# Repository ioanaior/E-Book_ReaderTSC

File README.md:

# E-Book_ReaderTSC

## 📘 Schema bloc

```mermaid
flowchart TB
  USB-C -->|5V| Charger["Battery Charger (MCP73832)"]
  Charger -->|Charging| LiPo["LiPo Battery"]
  LiPo --> LDO["3V3 LDO"]
  LiPo --> DC5["5V DC/DC"]

  ESP32["ESP32-C3-WROOM"]

  LDO -->|3.3V| ESP32
  LDO -->|3.3V| Display
  LDO -->|3.3V| SDCard
  LDO -->|3.3V| TempSensor
  LDO -->|3.3V| Buttons

  ESP32 -- SPI --> Display["1.5'' E-Ink Display (200x200px)"]
  ESP32 -- SPI --> SDCard["SD Card"]
  ESP32 -- GPIO --> Buttons["Buttons (3x)"]
  ESP32 -- I2C --> TempSensor["Temp/RH Sensor (BME680)"]
  ESP32 -- USB --> USB-C
```

# List of Components

Aici sunt listate componentele, impreuna cu linkurile pentru a verifica preturile si fisele tehnice. Unele componente nu au un model specificat, si în acele cazuri, fisele tehnice si linkurile catre preturi sunt marcate ca `#N/A`.
+ also SJ-ul si TP-urile sunt modelate de mine, deci nu am importat model 3D.

| Name of component  | Device                                    | Check Prices                                                                 | DataSheet                                                                  |
|--------------------|-------------------------------------------|-----------------------------------------------------------------------------|----------------------------------------------------------------------------|
| BOOT_BUTTON        | BUTTON_CUSYOMV1                           | [Check Price](https://industry.panasonic.com/global/en/products/control/switch/light-touch/number/evqpuj02k)  | [DataSheet](https://industry.panasonic.com/global/en/products/control/switch/light-touch/number/evqpuj02k) |
| C1                 | ESP32_WROVER_EAGLE-LTSPICE_CC0402         | [Check Price](https://industry.panasonic.com/global/en/products/control/switch/light-touch/number/evqpuj02k)  | [DataSheet](https://industry.panasonic.com/global/en/products/control/switch/light-touch/number/evqpuj02k) |
| C1_BAT             | ESP32_WROVER_EAGLE-LTSPICE_CC0402         | #N/A                                                                         | #N/A                                                                      |
| C1_BAT1            | EAGLE-LTSPICE_CC0402                      | #N/A                                                                         | #N/A                                                                      |
| C1_BAT2            | EAGLE-LTSPICE_CC0402                      | #N/A                                                                         | #N/A                                                                      |
| C2                 | ESP32_WROVER_EAGLE-LTSPICE_CC0402         | #N/A                                                                         | #N/A                                                                      |
| C2_BAT            | ESP32_WROVER_EAGLE-LTSPICE_CC0402         | #N/A                                                                         | #N/A                                                                      |
| C3                 | RCL_CPOL-EUCT3528                         | #N/A                                                                         | #N/A                                                                      |
| C4                 | ESP32_WROVER_EAGLE-LTSPICE_CC0402         | #N/A                                                                         | #N/A                                                                      |
| C4_USB             | ESP32_WROVER_EAGLE-LTSPICE_CC0402         | #N/A                                                                         | #N/A                                                                      |
| C5                 | ESP32_WROVER_EAGLE-LTSPICE_CC0402         | #N/A                                                                         | #N/A                                                                      |
| C5_USB             | ESP32_WROVER_EAGLE-LTSPICE_CC0402         | #N/A                                                                         | #N/A                                                                      |
| C6                 | ESP32_WROVER_EAGLE-LTSPICE_CC0402         | #N/A                                                                         | #N/A                                                                      |
| C7                 | ESP32_WROVER_EAGLE-LTSPICE_CC0402         | #N/A                                                                         | #N/A                                                                      |
| C8                 | ESP32_WROVER_EAGLE-LTSPICE_CC0402         | #N/A                                                                         | #N/A                                                                      |
| C9                 | EAGLE-LTSPICE_CC0402                      | #N/A                                                                         | #N/A                                                                      |
| C10                | ESP32_WROVER_EAGLE-LTSPICE_CC0402         | #N/A                                                                         | #N/A                                                                      |
| C10_SUPERCAP       | CPH3225A                                  | [Check Price](https://www.snapeda.com/parts/CPH3225A/Seiko+Instruments/view-part/?ref=eda) | [DataSheet](https://www.snapeda.com/parts/CPH3225A/Seiko+Instruments/view-part/?ref=eda) |
| CHANGE_BUTTON      | BUTTON_CUSYOMV1                           | [Check Price](https://industry.panasonic.com/global/en/products/control/switch-light-touch/number/evqpuj02k)  | [DataSheet](https://industry.panasonic.com/global/en/products/control/switch-light-touch/number/evqpuj02k) |
| CHG_LED            | ADAFRUIT_LEDCHIP-LED0603                  | [Check Price](https://www.snapeda.com/parts/KP-1608SURCK/Kingbright/view-part/?ref=search&t=LED%200603) | [DataSheet](https://www.snapeda.com/parts/KP-1608SURCK/Kingbright/view-part/?ref=search&t=LED%200603) |
| C_DELAY            | ESP32_WROVER_EAGLE-LTSPICE_CC0402         | #N/A                                                                         | #N/A                                                                      |
| D1                 | USBLC6-2SC6Y                              | [Check Price](https://www.snapeda.com/parts/USBLC6-2SC6Y/STMicroelectronics/view-part/?ref=eda) | [DataSheet](https://www.snapeda.com/parts/USBLC6-2SC6Y/STMicroelectronics/view-part/?ref=eda) |
| D2                 | ESP32_WROVER_AVX---SD0805S020S1R0_AVX_... | [Check Price](https://eu.mouser.com/ProductDetail/KYOCERA-AVX/SD0805S020S1R0?qs=jCA%252BPfw4LHbpkAoSnwrdjw%3D%3D) | [DataSheet](http://datasheets.avx.com/schottky.pdf)                       |
| D3                 | MBR0530                                   | [Check Price](https://eu.mouser.com/ProductDetail/KYOCERA-AVX/SD0805S020S1R0?qs=jCA%252BPfw4LHbpkAoSnwrdjw%3D%3D) | [DataSheet](https://eu.mouser.com/ProductDetail/KYOCERA-AVX/SD0805S020S1R0?qs=jCA%252BPfw4LHbpkAoSnwrdjw%3D%3D) |
| D4                 | MBR0530                                   | [Check Price](https://www.snapeda.com/parts/MBR0530/Onsemi/view-part/?ref=eda) | [DataSheet](https://www.snapeda.com/parts/MBR0530/Onsemi/view-part/?ref=eda) |
| D5                 | MBR0530                                   | [Check Price](https://www.snapeda.com/parts/MBR0530/Onsemi/view-part/?ref=eda) | [DataSheet](https://www.snapeda.com/parts/MBR0530/Onsemi/view-part/?ref=eda) |
| D6                 | PGB1010603MR                              | [Check Price](https://www.snapeda.com/parts/PGB1010603MR/Littelfuse/view-part/?ref=eda) | [DataSheet](https://www.snapeda.com/parts/PGB1010603MR/Littelfuse/view-part/?ref=eda) |
| D7                 | ESP32_WROVER_AVX---SD0805S020S1R0_AVX_... | [Check Price](https://eu.mouser.com/ProductDetail/KYOCERA-AVX/SD0805S020S1R0?qs=jCA%252BPfw4LHbpkAoSnwrdjw%3D%3D) | [DataSheet](http://datasheets.avx.com/schottky.pdf)                       |
| D8                 | PGB1010603MR                              | [Check Price](https://www.snapeda.com/parts/PGB1010603MR/Littelfuse/view-part/?ref=eda) | [DataSheet](https://www.snapeda.com/parts/PGB1010603MR/Littelfuse/view-part/?ref=eda) |
| D9                 | PGB1010603MR                              | [Check Price](https://www.snapeda.com/parts/PGB1010603MR/Littelfuse/view-part/?ref=eda) | [DataSheet](https://www.snapeda.com/parts/PGB1010603MR/Littelfuse/view-part/?ref=eda) |
| D10                | PGB1010603MR                              | [Check Price](https://www.snapeda.com/parts/PGB1010603MR/Littelfuse/view-part/?ref=eda) | [DataSheet](https://www.snapeda.com/parts/PGB1010603MR/Littelfuse/view-part/?ref=eda) |
| D11                | PGB1010603MR                              | [Check Price](https://www.snapeda.com/parts/PGB1010603MR/Littelfuse/view-part/?ref=eda) | [DataSheet](https://www.snapeda.com/parts/PGB1010603MR/Littelfuse/view-part/?ref=eda) |
| D12                | PGB1010603MR                              | [Check Price](https://www.snapeda.com/parts/PGB1010603MR/Littelfuse/view-part/?ref=eda) | [DataSheet](https://www.snapeda.com/parts/PGB1010603MR/Littelfuse/view-part/?ref=eda) |
| EPD_C1             | ESP32_WROVER_EAGLE-LTSPICE_CC0402         | #N/A                                                                         | #N/A                                                                      |
| EPD_C2             | ESP32_WROVER_EAGLE-LTSPICE_CC0402         | #N/A                                                                         | #N/A                                                                      |
| EPD_C5             | ESP32_WROVER_EAGLE-LTSPICE_CC0402         | #N/A                                                                         | #N/A                                                                      |
| EPD_C6             | ESP32_WROVER_EAGLE-LTSPICE_CC0402         | #N/A                                                                         | #N/A                                                                      |
| EPD_C7             | ESP32_WROVER_EAGLE-LTSPICE_CC0402         | #N/A                                                                         | #N/A                                                                      |
| EPD_C8             | ESP32_WROVER_EAGLE-LTSPICE_CC0402         | #N/A                                                                         | #N/A                                                                      |
| EPD_C9             | ESP32_WROVER_EAGLE-LTSPICE_CC0402         | #N/A                                                                         | #N/A                                                                      |
| EPD_C10            | ESP32_WROVER_EAGLE-LTSPICE_CC0402         | #N/A                                                                         | #N/A                                                                      |
| EPD_C11            | ESP32_WROVER_EAGLE-LTSPICE_CC0402         | #N/A                                                                         | #N/A                                                                      |
| EPD_C12            | ESP32_WROVER_EAGLE-LTSPICE_CC0402         | #N/A                                                                         | #N/A                                                                      |
| IC1                | BD5229G-TR                                | [Check Price](https://componentsearchengine.com/part-view/BD5229G-TR/ROHM%20Semiconductor) | [DataSheet](https://componentsearchengine.com/part-view/BD5229G-TR/ROHM%20Semiconductor) |
| IC4                | XC6220A331MR-G                            | [Check Price](https://componentsearchengine.com/part-view/XC6220A331MR-G/Torex) | [DataSheet](https://componentsearchengine.com/part-view/XC6220A331MR-G/Torex) |
| J1                 | FH34SRJ-24S-0.5SH_99_                     | [Check Price](https://componentsearchengine.com/part-view/XC6220A331MR-G/Torex) | [DataSheet](https://componentsearchengine.com/part-view/XC6220A331MR-G/Torex) |
| J2                 | SAMACSYS_PARTS_USB4110-GF-A               | [Check Price](https://componentsearchengine.com/part-view/USB4110-GF-A/GCT%20(GLOBAL%20CONNECTOR%20TECHNOLOGY)) | [DataSheet](https://componentsearchengine.com/part-view/USB4110-GF-A/GCT%20(GLOBAL%20CONNECTOR%20TECHNOLOGY)) |
| J3                 | QWIIC_CONNECTORJS-1MM                     | #N/A                                                                         | #N/A                                                                      |
| J4                 | 112A-TAAR-R03_ATTEND                      | [Check Price](https://store.comet.srl.ro/Catalogue/Product/43497/)           | [DataSheet](https://store.comet.srl.ro/Catalogue/Product/43497/)          |
| L1                 | 744043680IND_4828-WE-TPC_WRE              | [Check Price](https://eu.mouser.com/ProductDetail/Wurth-Elektronik/744043680?qs=PGXP4M47uW6VkZq%252BkzjrHA%3D%3D) | [DataSheet](https://eu.mouser.com/ProductDetail/Wurth-Elektronik/744043680?qs=PGXP4M47uW6VkZq%252BkzjrHA%3D%3D) |
| PFMF.050.1         | ESP32C6_VARISTORCN1812                    | [Check Price](https://www.mouser.co.uk/ProductDetail/EPCOS-TDK/B72520T0350K062?qs=dEfas%2FXlABIszF52uu7vrg%3D%3D) | [DataSheet](https://www.mouser.co.uk/ProductDetail/EPCOS-TDK/B72520T0350K062?qs=dEfas%2FXlABIszF52uu7vrg%3D%3D) |
| Q1                 | ESP32_WROVER_SPARKFUN-DISCRETESEMI_MOSFET_... | [Check Price](https://componentsearchengine.com/part-view/DMG2305UX-7/Diodes%20Incorporated) | [DataSheet](https://componentsearchengine.com/part-view/DMG2305UX-7/Diodes%20Incorporated) |
| Q2                 | ESP32_WROVER_SPARKFUN-DISCRETESEMI_MOSFET_... | #N/A                                                                         | #N/A                                                                      |
| Q3                 | D8                                        | [Check Price](https://componentsearchengine.com/part-view/PGB1010603MR/Littelfuse) | [DataSheet](https://componentsearchengine.com/part-view/PGB1010603MR/Littelfuse) |
| Q4                 | Q2_TS-B2_REACHPACK                        | #N/A                                                                         | #N/A                                                                      |

Detalii despre functionalitatea hardware

### Microcontroller – ESP32-C3-WROOM
Microcontroller-ul utilizat este ESP32-C3-WROOM, un procesor 32-bit RISC-V, care ruleaza la frecvente de pana la 160MHz. Acesta dispune de 512KB de SRAM intern si 8MB de flash extern, suficiente pentru a sustine aplicatii complexe. ESP32-C3-WROOM beneficiaza de conectivitate Wi-Fi 6 si Bluetooth 5, facilitand conexiuni rapide si stabile. Printre perifericele sale se numara SPI, I²C, UART si GPIO multiple, iar pentru economisirea energiei, dispune de moduri de tip sleep si deep sleep.

### Ecran E-Paper (1.5 inch)
Ecranul e-paper utilizat are o rezolutie de 200x200px si comunica cu ESP32 prin interfata SPI cu 4 pini (CS, DC, RST, BUSY). Desi consumul de energie este foarte redus in timpul afisarii statice, la fiecare refresh al imaginii ecranul necesita aproximativ 15–25mA, in functie de modul de actualizare ales. Acest tip de afisaj este ideal pentru aplicatiile de tip e-reader, datorita consumului minim de energie in mod static.

### Senzor de mediu – BME680
Senzorul BME680 masoara temperatura, umiditatea, presiunea si calitatea aerului (VOC/eCO2). Acesta comunica cu microcontroller-ul prin I²C la 400kHz, iar consumul in modul standby este de doar 2.1µA, crescand pana la cativa mA in timpul masurarilor. BME680 este o alegere excelenta datorita capacitatii sale de a integra multiple tipuri de masuratori intr-un singur cip, oferind date importante pentru monitorizarea mediului.

### Gestionarea energiei – Baterie Li-Po si IC de incarcare
Dispozitivul este alimentat de o baterie Li-Po de 2500mAh, care ofera o autonomie extinsa. IC-ul de incarcare MCP73832, compatibil cu incarcarea prin USB-C, permite incarcarea bateriei cu un curent de pana la 1A. Monitorizarea nivelului bateriei se face prin intermediul unui fuel gauge MAX17048, care transmite informatii despre tensiune si stare prin I²C. Pentru a asigura o tensiune stabila de 3.3V, se foloseste un regulator LDO XC6220A331MR-G, care alimenteaza microcontroller-ul si celelalte componente.

### Butoane tactile pentru interactiune
Dispozitivul dispune de trei butoane tactile pentru navigarea prin meniu, selectarea optiunilor si schimbarea paginilor. Fiecare buton este conectat la un GPIO al microcontroller-ului printr-un circuit de debouncing, care asigura o interactiune fiabila. Debouncing-ul poate fi implementat fie hardware, printr-o combinatie de rezistor si condensator, fie in firmware.

### Port USB-C
Portul USB-C permite atat incarcarea bateriei, cat si transferul de date. Acesta poate fi utilizat si pentru actualizari de firmware prin bootloader sau OTA prin Wi-Fi. Protectiile incluse (ESD si rezistente de terminare) asigura o protectie suplimentara impotriva eventualelor probleme de conectivitate.

### Conector Qwiic (I²C)
Conectorul Qwiic standardizat, cu patru pini (VCC, GND, SDA, SCL), faciliteaza integrarea rapida a modulelor I²C externe. Acesta este ideal pentru extinderea dispozitivului cu senzori suplimentari sau pentru prototipuri rapide.

### Card SD pentru stocare externa
Dispozitivul include un conector pentru card SD, permitand stocarea de e-book-uri, loguri sau fisiere pentru actualizari de firmware. Interfata poate fi configurata in modul SD (1-bit/4-bit) sau SPI, in functie de necesitatile firmware-ului.

### RTC DS3231
RTC-ul DS3231 asigura un ceas de timp real precis si mentine timpul chiar si atunci cand dispozitivul nu este alimentat, datorita unei baterii secundare sau supercondensatorului de backup. Comunicarea cu microcontroller-ul se face prin I²C.

### Memorie externa Flash (W25Q512JVEIQ)
Memoria flash externa W25Q512JVEIQ, conectata prin SPI dedicat (quad SPI), este utilizata pentru stocarea firmware-ului si a fisierelor mari (e-book-uri, etc.). Acesta permite o incarcare rapida a datelor si o capacitate mare de stocare.

### Comunicare si interfete
Dispozitivul utilizeaza diverse interfete pentru a comunica cu componentele sale:

- **SPI**: Ecranul e-paper si memoria flash externa utilizeaza SPI pentru comunicare.
- **I²C**: Senzorul BME680, fuel gauge MAX17048, RTC DS3231 si conectorul Qwiic sunt conectate prin I²C.
- **USB-C**: Transfer de date si alimentare.
- **GPIO**: Butoane tactile si semnale de control pentru display.

### Estimarea consumului de energie
- **ESP32-C3-WROOM** (activ): ~80mA (Wi-Fi activ) / < 10mA (idle)
- **E-Paper (refresh)**: ~15–25mA (doar in timpul refresh-ului)
- **BME680** (activ): ~3.6mA (peak) / 2.1µA (sleep)
- **MAX17048 (fuel gauge)**: ~50µA
- **DS3231 (RTC)**: ~3.5mA (activ) / <1µA (back-up)
- **MCP73832 (charger)**: Depinde de curentul de incarcare

In modul Deep Sleep, consumul total scade sub 50-100µA, iar in utilizare activa cu Wi-Fi si actualizari frecvente ale ecranului, consumul poate ajunge la 100-150mA.

Cu o baterie de 2500mAh, dispozitivul poate avea o autonomie de cateva saptamani in regim normal de utilizare, in care majoritatea timpului este in stare inactiva si doar afiseaza imagini statice.

## Detalierea pinilor ESP32-C6 utilizati pentru fiecare componenta

| Pin ESP32-C6  | Componenta / Semnal                       | Explicatie                                           |
|---------------|-------------------------------------------|------------------------------------------------------|
| GPIO1         | I²C SDA (BME688, MAX17048, DS3231, Qwiic) | Se foloseste pentru a partaja magistrala I²C intre toti senzorii si RTC. |
| GPIO2         | I²C SCL (BME688, MAX17048, DS3231, Qwiic) | Linia de clock pentru comunicarea I²C.              |
| GPIO5         | SPI MISO (E-Paper)                       | Pinul pentru citirea datelor sau a statusului de la ecranul e-paper. |
| GPIO6         | SPI MOSI (E-Paper)                       | Trimiterea datelor catre ecranul e-paper.            |
| GPIO7         | SPI CLK (E-Paper)                        | Semnal de clock pentru sincronizarea cu e-paper.    |
| GPIO8         | SPI CS (E-Paper)                         | Chip Select pentru a activa comunicarea cu e-paper.  |
| GPIO9         | E-Paper DC (Data/Command)                | Semnal pentru a diferentia intre date si comenzi pentru ecranul e-paper. |
| GPIO10        | E-Paper RST                              | Pinul de reset hardware pentru e-paper.              |
| GPIO11        | E-Paper BUSY                             | Intrare din display care indica daca ecranul este ocupat sau nu. |
| GPIO12        | Button #1                                | Intrare digitala pentru primul buton (ex. pagina urmatoare). |
| GPIO13        | Button #2                                | Intrare digitala pentru al doilea buton (ex. pagina anterioara). |
| GPIO14        | Button #3                                | Intrare digitala pentru al treilea buton (ex. Meniu/OK). |
| GPIO15        | MAX17048 ALERT (optional)                | Semnal de alerta de la MAX17048 pentru nivel scazut al bateriei. |
| GPIO16        | USB D+ (intern la USB PHY)               | Pin dedicat pentru semnalul USB 2.0 (D+).            |
| GPIO17        | USB D- (intern la USB PHY)               | Pin dedicat pentru semnalul USB 2.0 (D-).            |
| GPIO18        | LED de status (optional)                 | Indicator pentru diverse stari (ex. Wi-Fi, incarcare, etc.). |
| GPIO19        | SD Card CS (optional)                    | Chip Select pentru cardul SD (daca se foloseste SPI). |
| GPIO20        | SD Card MISO (optional)                  | Intrare date de la cardul SD.                        |
| GPIO21        | SD Card MOSI (optional)                  | Iesire date catre cardul SD.                         |
| GPIO4         | SD Card CLK (optional)                   | Semnal de clock pentru cardul SD (SPI).              |

## Concluzii

Acest proiect a fost un adevarat challenge si a implicat o cantitate considerabila de munca. Au existat momente cand m-am simtit complet depasita, iar uneori chiar enervata de complexitatea sa :)) Cu toate acestea, am reusit sa-l finalizez si sunt destul de multumita de rezultat. 
Sper ca totul este in regula si ca nu mi-a scapat vreun detaliu prea important. Ca orice proiect de acest tip, a fost o experienta de invatare continua, iar daca voi gasi ceva ce nu am luat in considerare, il voi imbunatati pe parcurs.😅<3

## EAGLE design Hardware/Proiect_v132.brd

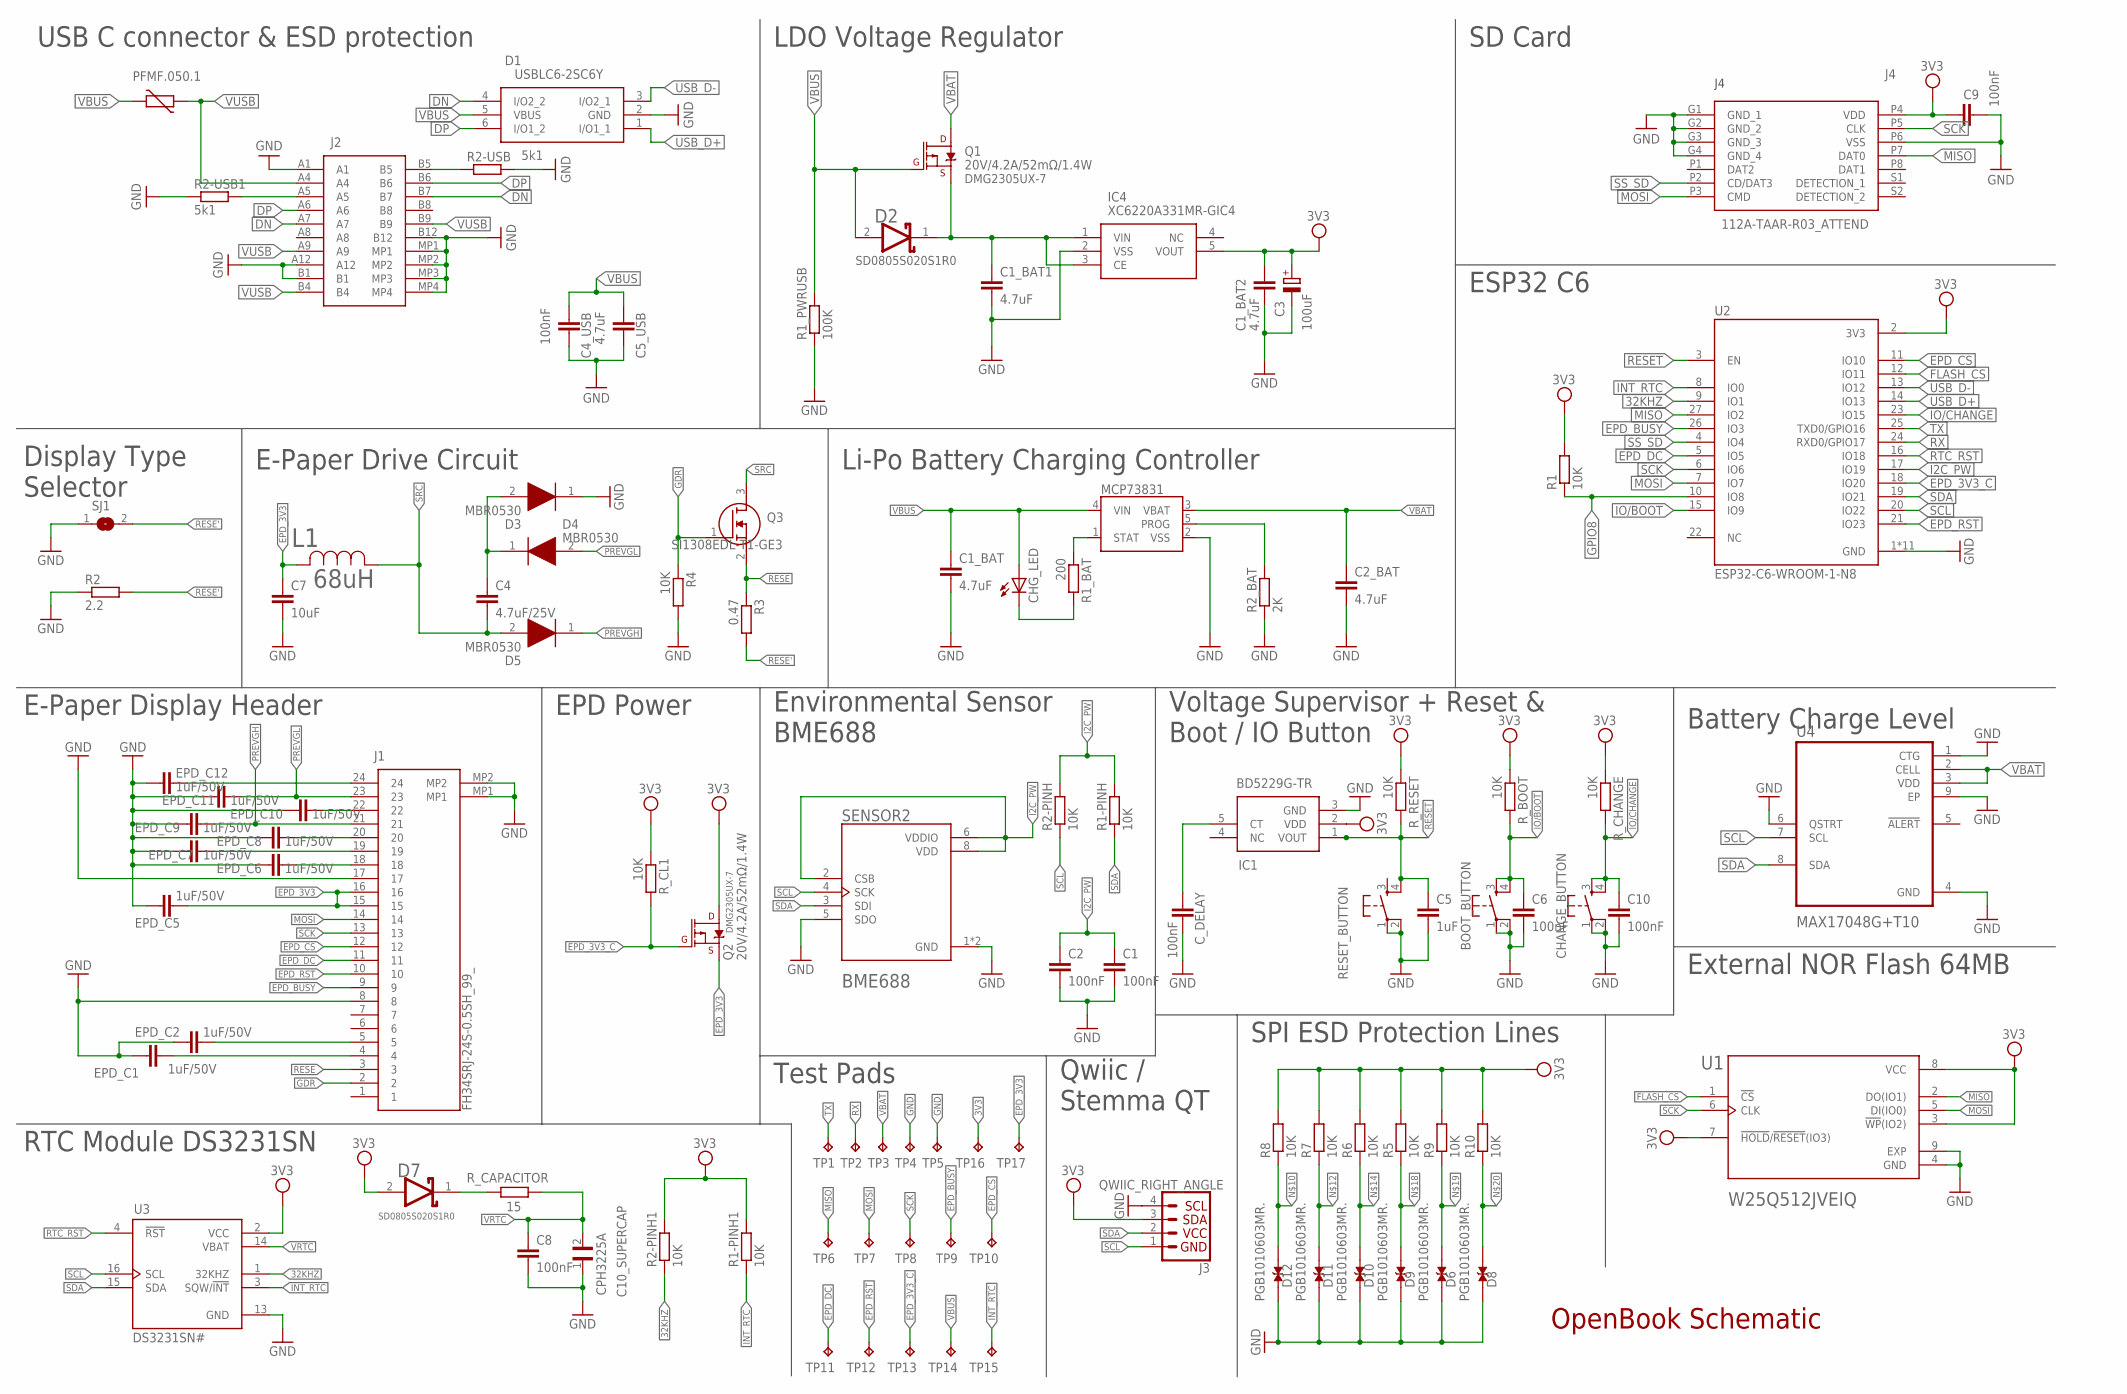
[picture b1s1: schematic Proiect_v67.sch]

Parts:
BOOT_BUTTON: BUTTON_CUSYOMV1.; MYBUTTON
C1, C2, C4_USB, C6, C8, C9, C10: 100nF; EAGLE-LTSPICE_C0402
C1_BAT, C1_BAT1, C1_BAT2, C2_BAT, C5_USB: 4.7uF; EAGLE-LTSPICE_C0402
C3: 100uF; RCL_CT3528
C4: 4.7uF/25V; EAGLE-LTSPICE_C0402
C5: 1uF; EAGLE-LTSPICE_C0402
C7: 10uF; EAGLE-LTSPICE_C0402
C10_SUPERCAP: CPH3225A; CAPCP3225X100N
CHANGE_BUTTON: BUTTON_CUSYOMV1.; MYBUTTON
CHG_LED: ADAFRUIT_LEDCHIP-LED0603; ADAFRUIT_CHIP-LED0603
C_DELAY: 100nF; EAGLE-LTSPICE_C0402
D1: USBLC6-2SC6Y; SOT95P280X145-6N
D2, D7: ESP32_WROVER_AVX---SD0805S020S1R0_AVX_SD0805S020S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; ESP32_WROVER_AVX---SD0805S020S1R0_AVX_SD0805S020S1R0_0
D3, D4, D5: MBR0530; SOD3716X135N
D6, D8, D9, D10, D11, D12: PGB1010603MR.; DIOC1608X36N
EPD_C1, EPD_C2, EPD_C5, EPD_C6, EPD_C7, EPD_C8, EPD_C9, EPD_C10, EPD_C11, EPD_C12: 1uF/50V; EAGLE-LTSPICE_C0402
IC1: BD5229G-TR; SOT95P280X125-5N
IC4: XC6220A331MR-GIC4; SOT95P280X120-5N
J1: FH34SRJ-24S-0.5SH_99_; FH34SRJ24S05SH99
J2: SAMACSYS_PARTS_USB4110-GF-A; SAMACSYS_PARTS_USB4110GFA
J3: QWIIC_RIGHT_ANGLE; JST04_1MM_RA
J4: 112A-TAAR-R03_ATTEND; 112ATAARR03ATTEND
L1: 68uH; IND_4828-WE-TPC_WRE
MCP73831: ESP32_WROVER_SPARKFUN-IC-POWER_MCP73831; ESP32_WROVER_SPARKFUN-IC-POWER_SOT23-5
PFMF.050.1: ESP32C6_VARISTORCN1812; ESP32C6_VARISTOR_CT/CN1812
Q1, Q2: 20V/4.2A/52mΩ/1.4W; ESP32_WROVER_SPARKFUN-DISCRETESEMI_SOT23-3
Q3: SI1308EDL-T1-GE3; SOT65P210X110-3N
R1, R1-PINH, R1-PINH1, R2-PINH, R2-PINH1, R4, R5, R6, R7, R8, R9, R10: 10K; ESP32_WROVER_EAGLE-LTSPICE_R0402
R1_BAT: 200; ESP32_WROVER_EAGLE-LTSPICE_R0402
R1_PWRUSB: 100K; ESP32_WROVER_EAGLE-LTSPICE_R0402
R2: 2.2; ESP32_WROVER_EAGLE-LTSPICE_R0402
R2-USB, R2-USB1: 5k1; ESP32_WROVER_EAGLE-LTSPICE_R0402
R2_BAT: 2K; ESP32_WROVER_EAGLE-LTSPICE_R0402
R3: 0.47; ESP32_WROVER_EAGLE-LTSPICE_R0402
RESET_BUTTON: BUTTON_CUSYOMV1.; MYBUTTON
R_BOOT: 10K; ESP32_WROVER_EAGLE-LTSPICE_R0402
R_CAPACITOR: 15; ESP32_WROVER_EAGLE-LTSPICE_R0402
R_CHANGE: 10K; ESP32_WROVER_EAGLE-LTSPICE_R0402
R_CL1: 10K; ESP32_WROVER_EAGLE-LTSPICE_R0402
R_RESET: 10K; ESP32_WROVER_EAGLE-LTSPICE_R0402
SENSOR2: ESP32_WROVER_BME680_BME680; ESP32_WROVER_BME680_PSON80P300X300X100-8N
SJ1: SJ
TP1, TP2, TP3, TP4, TP5, TP6, TP7, TP8, TP9, TP10, TP11, TP12, TP13, TP14, TP15, TP16, TP17: TPTP20R; TP20R
U1: W25Q512JVEIQ; SON127P600X800X80-9N
U2: ESP32-C6-WROOM-1-N8; XCVR_ESP32-C6-WROOM-1-N8
U3: DS3231SN#; SOIC127P1032X265-16N
U4: MAX17048G+T10; SON50P200X200X80-9N

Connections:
3V3: C1_BAT2.1, C3.+, C9.1, D7.2 (ANODE), IC1.2 (VDD), IC4.5 (VOUT), J3.3, J4.P4 (VDD), Q2.3 (D), R1.2, R1-PINH1.2, R2-PINH1.2, R5.2, R6.2, R7.2, R8.2, R9.2, R10.2, R_BOOT.1, R_CHANGE.1, R_CL1.1, R_RESET.1, TP16.TP, U1.3 (!WP!(IO2)), U1.7 (!HOLD!/!RESET!(IO3)), U1.8 (VCC), U2.2 (3V3), U3.2 (VCC)
32KHZ: R2-PINH1.1, U2.9 (IO1), U3.1 (32KHZ)
DN: D1.4 (I/O2_2), J2.A7, J2.B7
DP: D1.6 (I/O1_2), J2.A6, J2.B6
EPD_3V3: C7.1, EPD_C5.1, J1.15, J1.16, L1.2, Q2.2 (S), TP17.TP
EPD_3V3_C: Q2.1 (G), R_CL1.2, TP13.TP, U2.18 (IO20)
EPD_BUSY: J1.9, TP9.TP, U2.26 (IO3)
EPD_CS: J1.12, TP10.TP, U2.11 (IO10)
EPD_DC: J1.11, TP11.TP, U2.5 (IO5)
EPD_RST: J1.10, TP12.TP, U2.21 (IO23)
FLASH_CS: U1.1 (!CS), U2.12 (IO11)
GDR: J1.2, Q3.1 (G), R4.1
GND: BOOT_BUTTON.1, BOOT_BUTTON.2, C1.2, C1_BAT.2, C1_BAT1.2, C1_BAT2.2, C2.2, C2_BAT.2, C3.-, C4_USB.2, C5.2, C5_USB.2, C6.2, C7.2, C8.2, C9.2, C10.2, C10_SUPERCAP.1, CHANGE_BUTTON.1, CHANGE_BUTTON.2, C_DELAY.2, D1.2 (GND), D3.1 (K), D6.1, D8.1, D9.1, D10.1, D11.1, D12.1, EPD_C1.2, EPD_C2.2, EPD_C5.2, EPD_C6.2, EPD_C7.2, EPD_C8.2, EPD_C9.2, EPD_C10.2, EPD_C11.2, EPD_C12.2, IC1.3 (GND), IC4.2 (VSS), J1.8, J1.17, J1.MP1, J1.MP2, J2.A1, J2.A12, J2.B1, J2.B12, J2.MP1, J2.MP2, J2.MP3, J2.MP4, J3.4, J4.G1 (GND_1), J4.G2 (GND_2), J4.G3 (GND_3), J4.G4 (GND_4), J4.P6 (VSS), MCP73831.2 (VSS), R1_PWRUSB.1, R2.1, R2-USB.2, R2-USB1.1, R2_BAT.1, R4.2, RESET_BUTTON.1, RESET_BUTTON.2, SENSOR2.1 (GND), SENSOR2.5 (SDO), SENSOR2.7 (GND), SJ1.1, TP4.TP, TP5.TP, U1.4 (GND), U1.9 (EXP), U2.1 (GND), U2.28 (GND), U2.29_1 (GND), U2.29_2 (GND), U2.29_3 (GND), U2.29_4 (GND), U2.29_5 (GND), U2.29_6 (GND), U2.29_7 (GND), U2.29_8 (GND), U2.29_9 (GND), U3.13 (GND), U4.1 (CTG), U4.4 (GND), U4.6 (QSTRT), U4.9 (EP)
GPIO8: R1.1, U2.10 (IO8)
I2C_PW: C1.1, C2.1, R1-PINH.2, R2-PINH.2, SENSOR2.2 (CSB), SENSOR2.6 (VDDIO), SENSOR2.8 (VDD), U2.17 (IO19)
INT_RTC: R1-PINH1.1, TP15.TP, U2.8 (IO0), U3.3 (SQW/!INT)
IO/BOOT: BOOT_BUTTON.3, BOOT_BUTTON.4, C6.1, R_BOOT.2, U2.15 (IO9)
IO/CHANGE: C10.1, CHANGE_BUTTON.3, CHANGE_BUTTON.4, R_CHANGE.2, U2.23 (IO15)
MISO: J4.P7 (DAT0), TP6.TP, U1.2 (DO(IO1)), U2.27 (IO2)
MOSI: J1.14, J4.P3 (CMD), TP7.TP, U1.5 (DI(IO0)), U2.7 (IO7)
unnamed: J2.B5, R2-USB.1
unnamed: C_DELAY.1, IC1.5 (CT)
unnamed: EPD_C12.1, J1.24
unnamed: C1_BAT1.1, D2.1 (CATHODE), IC4.1 (VIN), IC4.3 (CE), Q1.2 (S)
unnamed: MCP73831.5 (PROG), R2_BAT.2
unnamed: CHG_LED.C, R1_BAT.2
unnamed: MCP73831.1 (STAT), R1_BAT.1
unnamed: C4.1, D3.2 (A), D4.1 (K)
unnamed: D12.2, R8.1
unnamed: J2.A5, R2-USB1.2
unnamed: D11.2, R7.1
unnamed: EPD_C10.1, J1.22
unnamed: D10.2, R6.1
unnamed: EPD_C8.1, J1.20
unnamed: EPD_C7.1, J1.19
unnamed: EPD_C6.1, J1.18
unnamed: D9.2, R5.1
unnamed: D6.2, R9.1
unnamed: D8.2, R10.1
unnamed: D7.1 (CATHODE), R_CAPACITOR.2
unnamed: EPD_C2.1, J1.5
unnamed: EPD_C1.1, J1.4
PREVGH: D5.1 (K), EPD_C9.1, J1.21
PREVGL: D4.2 (A), EPD_C11.1, J1.23
RESE: J1.3, Q3.2 (S), R3.1
RESE': R2.2, R3.2, SJ1.2
RESET: C5.1, IC1.1 (VOUT), RESET_BUTTON.4, R_RESET.2, U2.3 (EN)
RTC_RST: U2.16 (IO18), U3.4 (!RST)
RX: TP2.TP, U2.24 (RXD0/GPIO17)
SCK: J1.13, J4.P5 (CLK), TP8.TP, U1.6 (CLK), U2.6 (IO6)
SCL: J3.1, R2-PINH.1, SENSOR2.4 (SCK), U2.20 (IO22), U3.16 (SCL), U4.7 (SCL)
SDA: J3.2, R1-PINH.1, SENSOR2.3 (SDI), U2.19 (IO21), U3.15 (SDA), U4.8 (SDA)
SRC: C4.2, D5.2 (A), L1.1, Q3.3 (D)
SS_SD: J4.P2 (CD/DAT3), U2.4 (IO4)
TX: TP1.TP, U2.25 (TXD0/GPIO16)
USB_D+: D1.1 (I/O1_1), U2.14 (IO13)
USB_D-: D1.3 (I/O2_1), U2.13 (IO12)
VBAT: C2_BAT.1, MCP73831.3 (VBAT), Q1.3 (D), TP3.TP, U4.2 (CELL), U4.3 (VDD)
VBUS: C1_BAT.1, C4_USB.1, C5_USB.1, CHG_LED.A, D1.5 (VBUS), D2.2 (ANODE), MCP73831.4 (VIN), PFMF.050.1.2, Q1.1 (G), R1_PWRUSB.2, TP14.TP
VRTC: C8.1, C10_SUPERCAP.2, R_CAPACITOR.1, U3.14 (VBAT)
VUSB: J2.A4, J2.A9, J2.B4, J2.B9, PFMF.050.1.1

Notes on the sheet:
USB C connector & ESD protection
LDO Voltage Regulator
SD Card
ESP32 C6
Battery Charge Level
Voltage Supervisor + Reset & Boot / IO Button
Environmental Sensor BME688
EPD Power
E-Paper Display Header
Display Type Selector
E-Paper Drive Circuit
Li-Po Battery Charging Controller
RTC Module DS3231SN
Test Pads
Qwiic / Stemma QT
SPI ESD Protection Lines
External NOR Flash 64MB
OpenBook Schematic

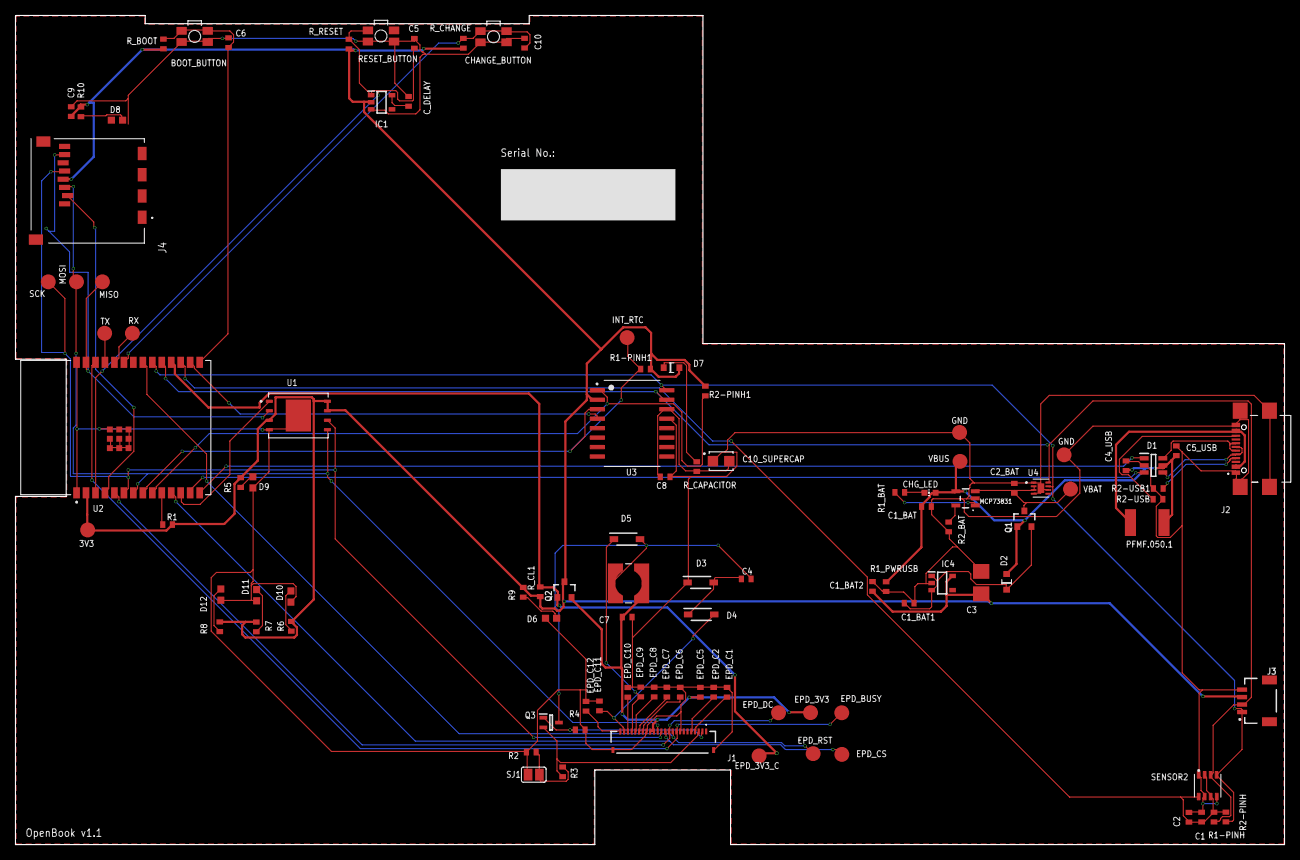
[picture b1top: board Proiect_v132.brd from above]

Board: 2 copper layers, 170.2 x 111.2 mm, 103 parts (0 on the bottom side), 61 nets.

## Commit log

2025-04-06 mermaid Readme
2025-04-06 am adaugat Hardware
2025-04-06 am adaugat si restul folderelor
2025-04-11 am rezolvat issue-urile
2025-04-11 am rezolvat issue-urile si am adaugat fisierele

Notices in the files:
parts and their libraries:
COPYRIGHT: Copyright (C) 2024 Ultra Librarian. All rights reserved.
